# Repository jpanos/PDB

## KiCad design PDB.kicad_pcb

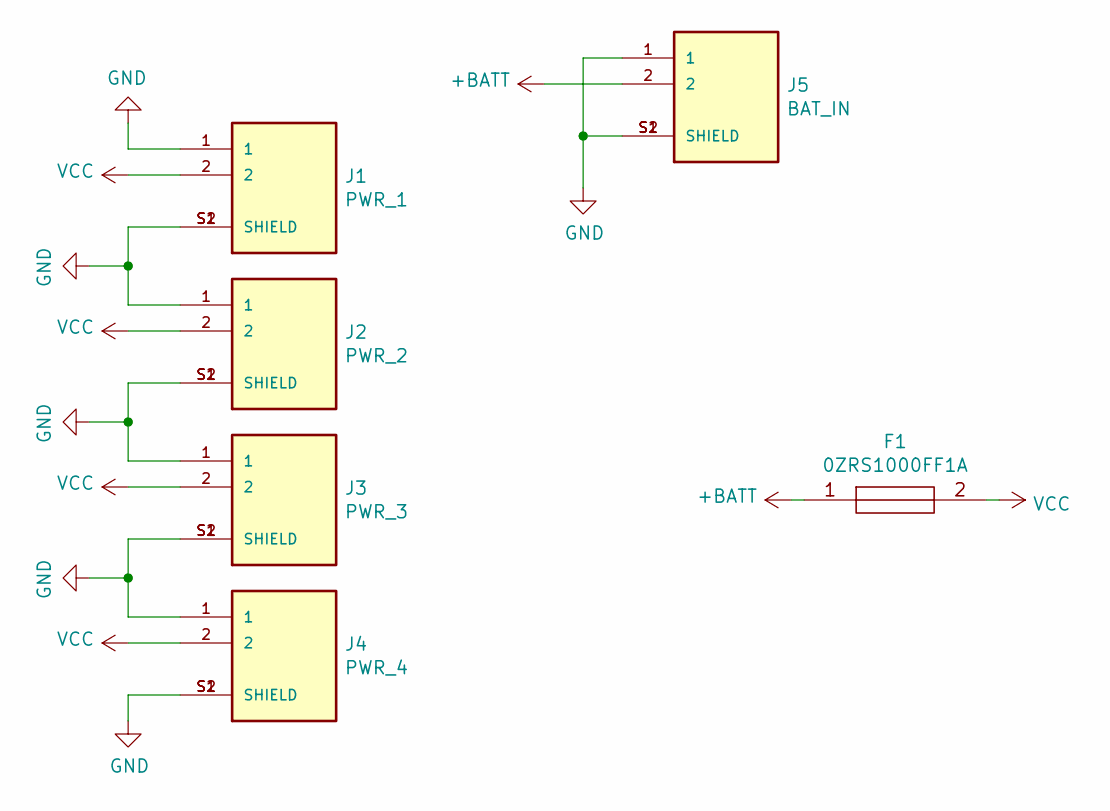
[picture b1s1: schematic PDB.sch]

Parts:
F1: 0ZRS1000FF1A; Manufacturer_Part_Number 0ZRS1000FF1A; Mouser Part Number 530-0ZRS1000FF1A
J1: PWR_1; AMASS_XT60PW-F; PARTREV V1.2
J2: PWR_2; AMASS_XT60PW-F; PARTREV V1.2
J3: PWR_3; AMASS_XT60PW-F; PARTREV V1.2
J4: PWR_4; AMASS_XT60PW-F; PARTREV V1.2
J5: BAT_IN; AMASS_XT60PW-F; PARTREV V1.2

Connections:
+BATT: F1.1, J5.2
GND: J1.1, J1.S1 (SHIELD), J1.S2 (SHIELD), J2.1, J2.S1 (SHIELD), J2.S2 (SHIELD), J3.1, J3.S1 (SHIELD), J3.S2 (SHIELD), J4.1, J4.S1 (SHIELD), J4.S2 (SHIELD), J5.1, J5.S1 (SHIELD), J5.S2 (SHIELD)
VCC: F1.2, J1.2, J2.2, J3.2, J4.2

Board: 2 copper layers, 6 parts (0 on the bottom side), 3 nets, no tracks yet.

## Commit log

2021-06-16 PDB board REV 1
2021-06-16 testing
